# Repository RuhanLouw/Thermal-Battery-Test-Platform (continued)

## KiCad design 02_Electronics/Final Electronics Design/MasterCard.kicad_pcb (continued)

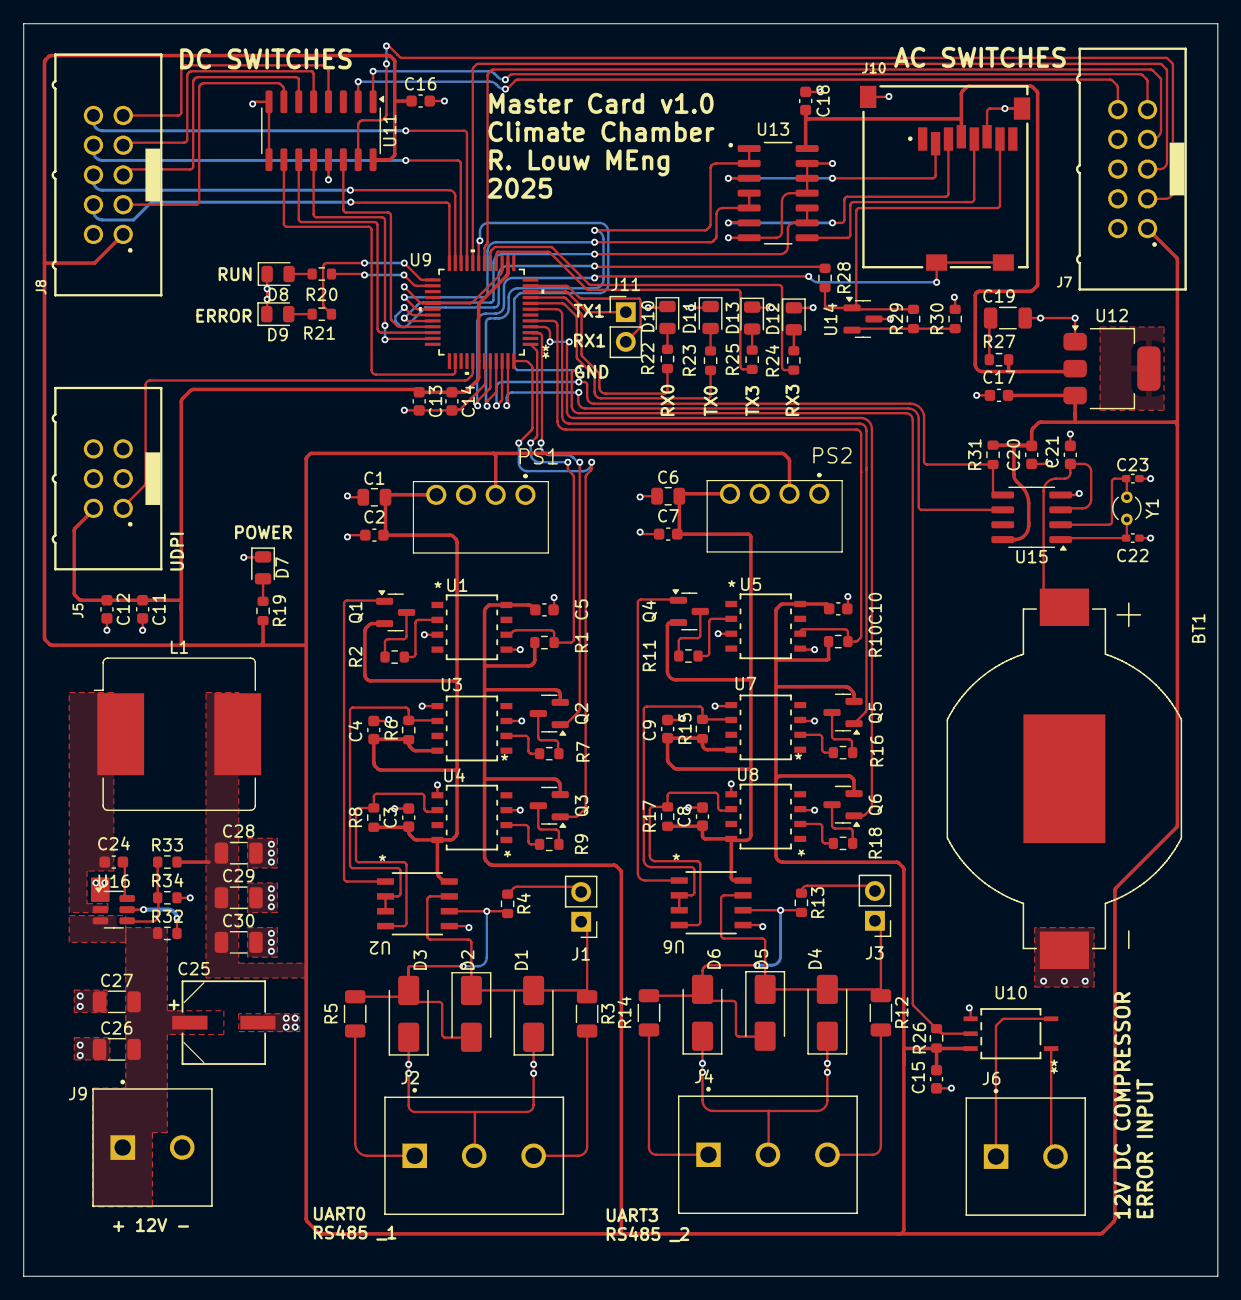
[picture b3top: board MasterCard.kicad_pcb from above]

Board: 2 copper layers, 102.0 x 107.0 mm, 115 parts (0 on the bottom side), 96 nets.

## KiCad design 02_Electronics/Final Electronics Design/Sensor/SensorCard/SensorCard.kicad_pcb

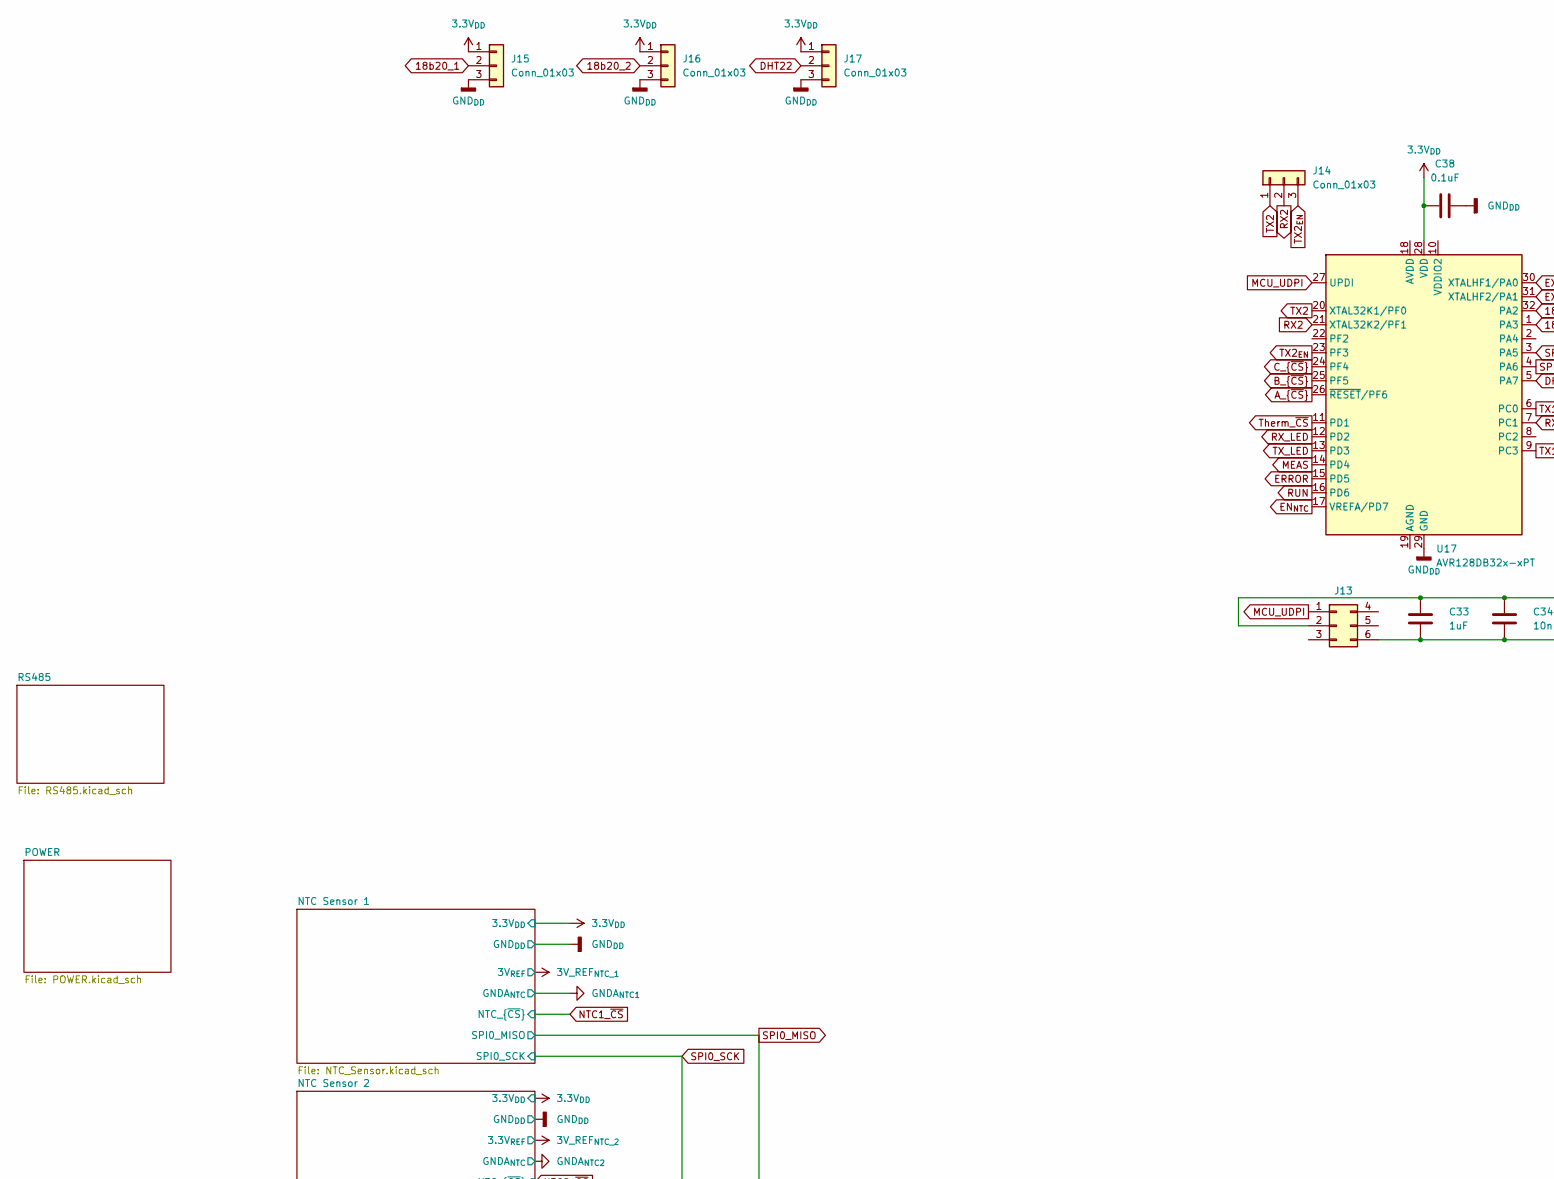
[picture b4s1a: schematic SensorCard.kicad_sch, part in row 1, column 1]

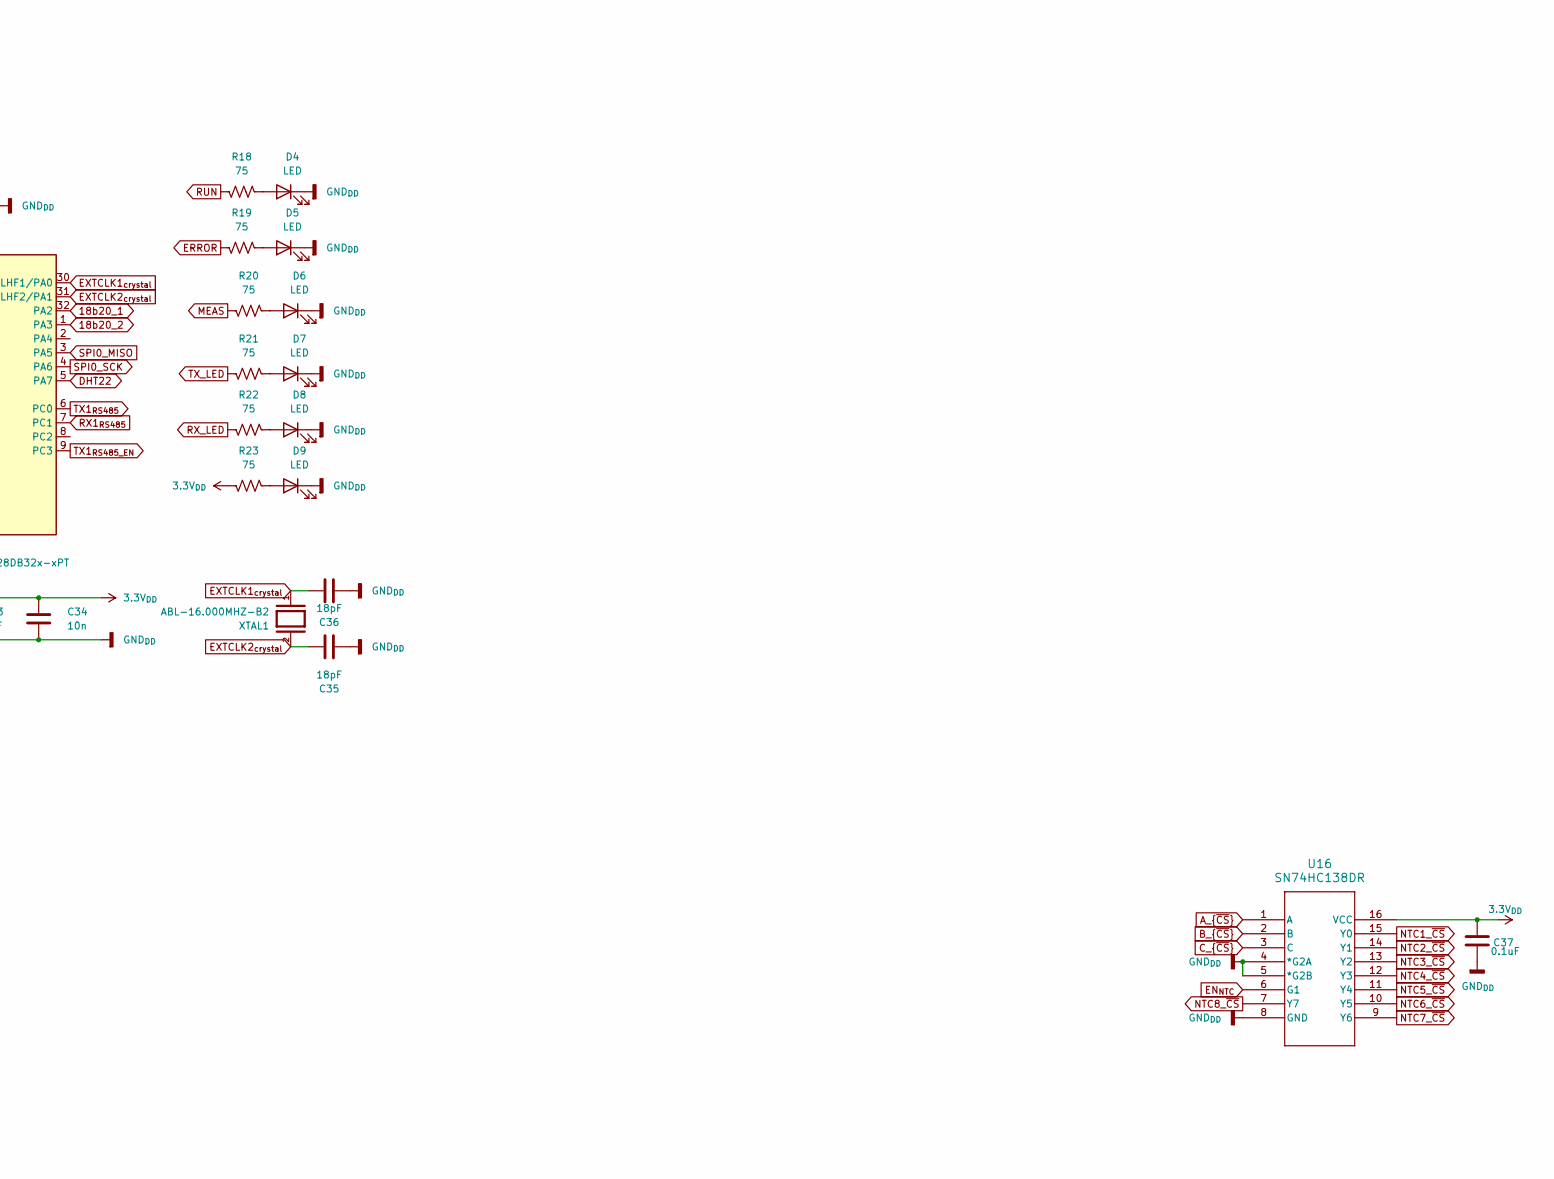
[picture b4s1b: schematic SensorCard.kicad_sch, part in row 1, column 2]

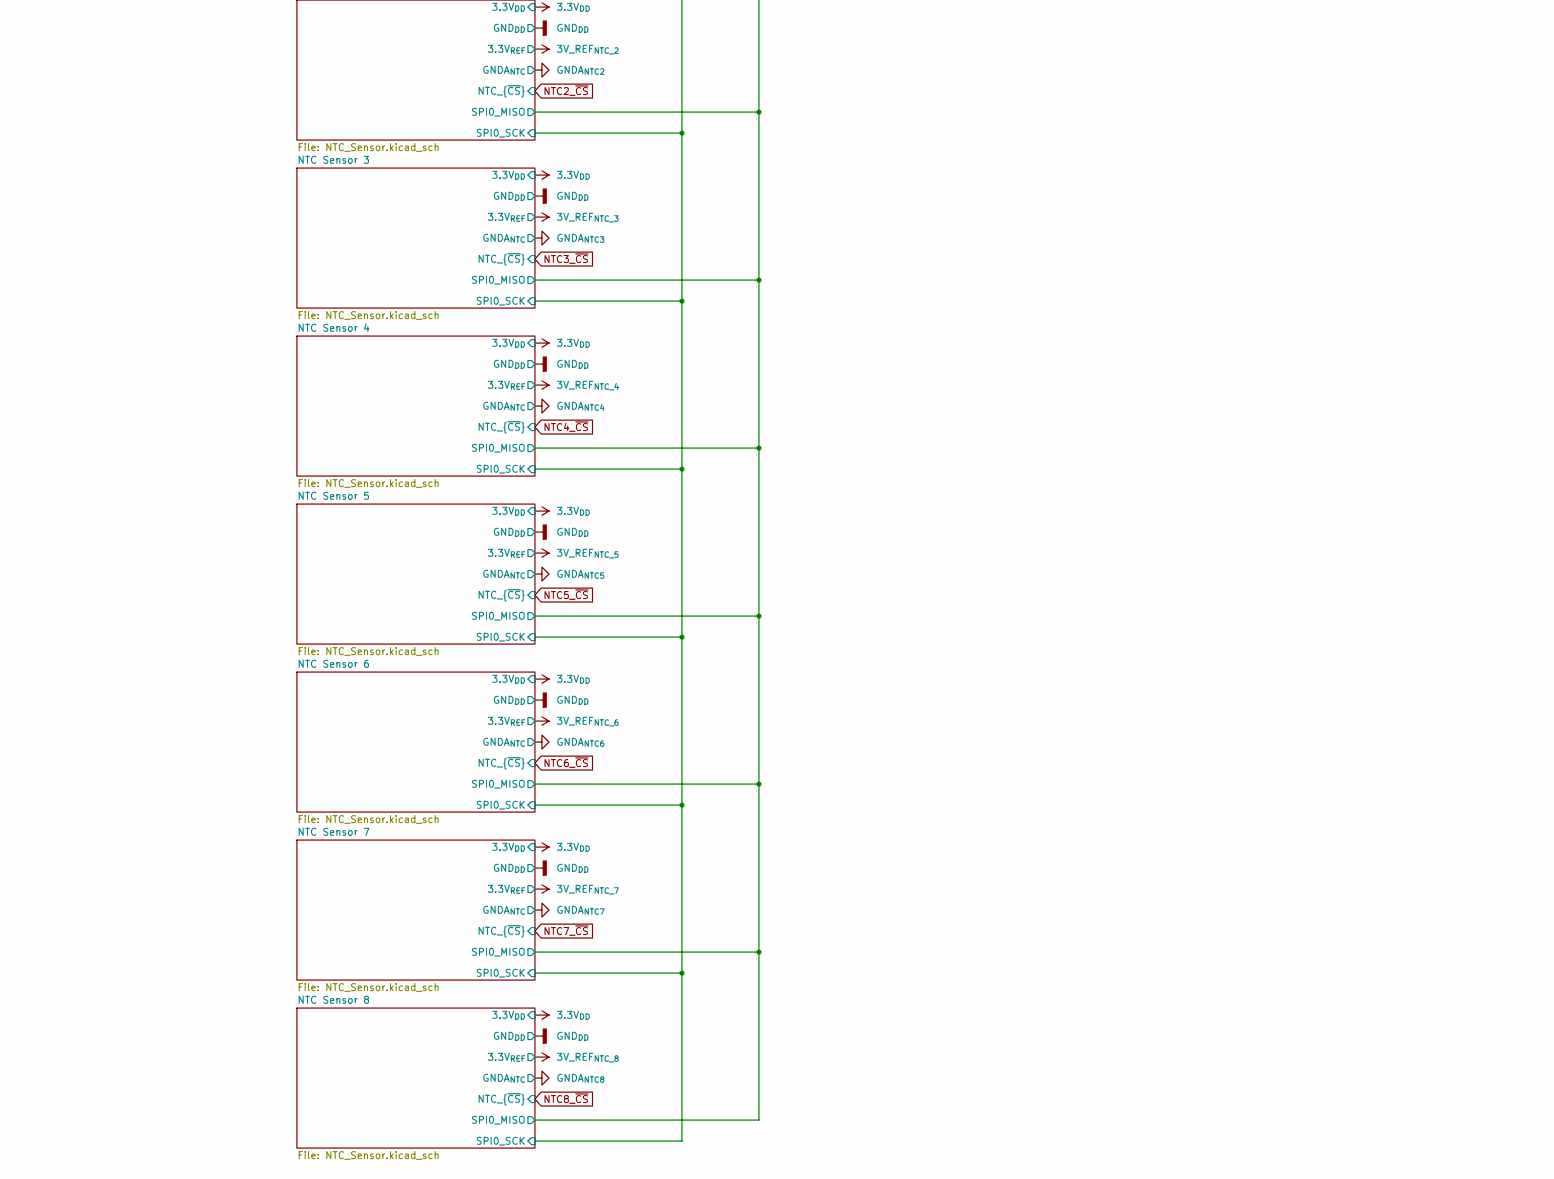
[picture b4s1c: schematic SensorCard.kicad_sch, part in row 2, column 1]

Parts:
C33: 1uF; C_0603_1608Metric
C34: 10n; C_0603_1608Metric
C35, C36: 18pF; C_0402_1005Metric
C37, C38: 0.1uF; C_0603_1608Metric
D4, D5, D6, D7, D8, D9: LED; LED_0805_2012Metric
J13: Conn_02x03_Top_Bottom; 61200621621
J14: Conn_01x03; PinHeader_1x03_P2.54mm_Vertical
J15, J16, J17: Conn_01x03; JST_XH_B3B-XH-A_1x03_P2.50mm_Vertical
R18, R19, R20, R21, R22, R23: 75; R_0603_1608Metric
U16: SN74HC138DR
U17: AVR128DB32x-xPT; TQFP-32_7x7mm_P0.8mm
XTAL1: ABL-16.000MHZ-B2; XTAL_HC49P488W46L1150T500H350; PARTREV 03.27.2018

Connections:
18b20_1: J15.2, U17.32 (PA2)
18b20_2: J16.2, U17.1 (PA3)
A_{~CS}: U16.1 (A), U17.26 (~RESET/PF6)
B_{~CS}: U16.2 (B), U17.25 (PF5)
C_{~CS}: U16.3 (C), U17.24 (PF4)
DHT22: J17.2, U17.5 (PA7)
EN_{NTC}: U16.6 (G1), U17.17 (VREFA/PD7)
ERROR: R19.1, U17.15 (PD5)
EXTCLK1_{crystal}: C36.1, U17.30 (XTALHF1/PA0), XTAL1.1
EXTCLK2_{crystal}: C35.1, U17.31 (XTALHF2/PA1), XTAL1.2
MCU_UDPI: J13.1, U17.27 (UPDI)
MEAS: R20.1, U17.14 (PD4)
NTC1_~CS: U16.15 (Y0); also elsewhere on the board
NTC2_~CS: U16.14 (Y1); also elsewhere on the board
NTC3_~CS: U16.13 (Y2); also elsewhere on the board
NTC4_~CS: U16.12 (Y3); also elsewhere on the board
NTC5_~CS: U16.11 (Y4); also elsewhere on the board
NTC6_~CS: U16.10 (Y5); also elsewhere on the board
NTC7_~CS: U16.9 (Y6); also elsewhere on the board
NTC8_~CS: U16.7 (Y7); also elsewhere on the board
unnamed: D4.2 (A), R18.2
unnamed: D5.2 (A), R19.2
unnamed: D6.2 (A), R20.2
unnamed: D7.2 (A), R21.2
unnamed: D8.2 (A), R22.2
unnamed: D9.2 (A), R23.2
RUN: R18.1, U17.16 (PD6)
RX1_{RS485}: U17.7 (PC1); also elsewhere on the board
RX2: J14.2, U17.21 (XTAL32K2/PF1)
RX_LED: R22.1, U17.12 (PD2)
SPI0_MISO: U17.3 (PA5); also elsewhere on the board
SPI0_SCK: U17.4 (PA6); also elsewhere on the board
TX1_{RS485_EN}: U17.9 (PC3); also elsewhere on the board
TX1_{RS485}: U17.6 (PC0); also elsewhere on the board
TX2: J14.1, U17.20 (XTAL32K1/PF0)
TX2_{EN}: J14.3, U17.23 (PF3)
TX_LED: R21.1, U17.13 (PD3)
Therm_~CS: U17.11 (PD1); also elsewhere on the board

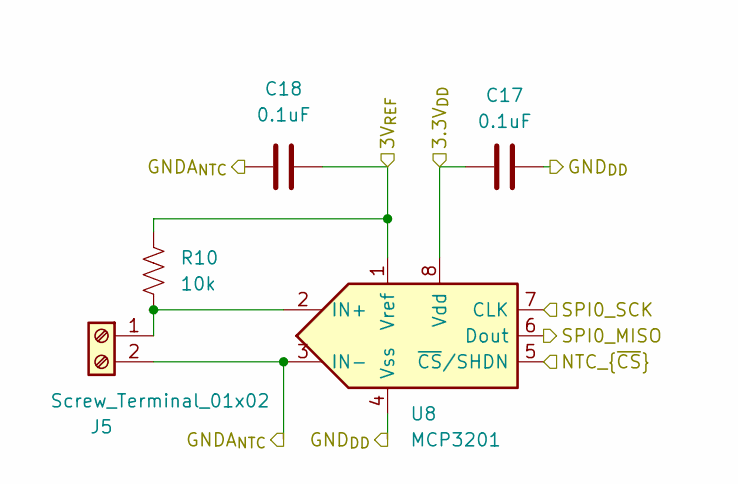
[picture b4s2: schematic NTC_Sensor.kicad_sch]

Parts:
C17, C18: 0.1uF; C_0603_1608Metric
J5: Screw_Terminal_01x02; TERM BLOCK 2P HORIZON 2.54MM PCB
R10: 10k; R_1206_3216Metric
U8: MCP3201; SOIC8-N_MC_MCH

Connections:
3V_REF_{NTC_1}: C18.2, R10.1, U8.1 (Vref); also elsewhere on the board
GNDA_{NTC1}: C18.1, J5.2, U8.3 (IN-); also elsewhere on the board
NTC1_~CS: U8.5 (~CS/SHDN); also elsewhere on the board
unnamed: J5.1, R10.2, U8.2 (IN+)
SPI0_MISO: U8.6 (Dout); also elsewhere on the board
SPI0_SCK: U8.7 (CLK); also elsewhere on the board

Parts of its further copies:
C19, C20, C21, C22, C23, C24, C25, C26, C27, C28, C29, C30, C31, C32: 0.1uF; C_0603_1608Metric
J6, J7, J8, J9, J10, J11, J12: Screw_Terminal_01x02; TERM BLOCK 2P HORIZON 2.54MM PCB
R11, R12, R13, R14, R15, R16, R17: 10k; R_1206_3216Metric
U9, U10, U11, U12, U13, U14, U15: MCP3201; SOIC8-N_MC_MCH

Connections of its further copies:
3V_REF_{NTC_2}: C20.2, R11.1, U9.1 (Vref); also elsewhere on the board
3V_REF_{NTC_3}: C22.2, R12.1, U10.1 (Vref); also elsewhere on the board
3V_REF_{NTC_4}: C24.2, R13.1, U11.1 (Vref); also elsewhere on the board
3V_REF_{NTC_5}: C26.2, R14.1, U12.1 (Vref); also elsewhere on the board
3V_REF_{NTC_6}: C28.2, R15.1, U13.1 (Vref); also elsewhere on the board
3V_REF_{NTC_7}: C30.2, R16.1, U14.1 (Vref); also elsewhere on the board
3V_REF_{NTC_8}: C32.2, R17.1, U15.1 (Vref); also elsewhere on the board
GNDA_{NTC2}: C20.1, J6.2, U9.3 (IN-); also elsewhere on the board
GNDA_{NTC3}: C22.1, J7.2, U10.3 (IN-); also elsewhere on the board
GNDA_{NTC4}: C24.1, J8.2, U11.3 (IN-); also elsewhere on the board
GNDA_{NTC5}: C26.1, J9.2, U12.3 (IN-); also elsewhere on the board
GNDA_{NTC6}: C28.1, J10.2, U13.3 (IN-); also elsewhere on the board
GNDA_{NTC7}: C30.1, J11.2, U14.3 (IN-); also elsewhere on the board
GNDA_{NTC8}: C32.1, J12.2, U15.3 (IN-); also elsewhere on the board
NTC2_~CS: U9.5 (~CS/SHDN); also elsewhere on the board
NTC3_~CS: U10.5 (~CS/SHDN); also elsewhere on the board
NTC4_~CS: U11.5 (~CS/SHDN); also elsewhere on the board
NTC5_~CS: U12.5 (~CS/SHDN); also elsewhere on the board
NTC6_~CS: U13.5 (~CS/SHDN); also elsewhere on the board
NTC7_~CS: U14.5 (~CS/SHDN); also elsewhere on the board
NTC8_~CS: U15.5 (~CS/SHDN); also elsewhere on the board
unnamed: J6.1, R11.2, U9.2 (IN+)
unnamed: J7.1, R12.2, U10.2 (IN+)
unnamed: J8.1, R13.2, U11.2 (IN+)
unnamed: J9.1, R14.2, U12.2 (IN+)
unnamed: J10.1, R15.2, U13.2 (IN+)
unnamed: J11.1, R16.2, U14.2 (IN+)
unnamed: J12.1, R17.2, U15.2 (IN+)
SPI0_MISO: U9.6 (Dout), U10.6 (Dout), U11.6 (Dout), U12.6 (Dout), U13.6 (Dout), U14.6 (Dout), U15.6 (Dout); also elsewhere on the board
SPI0_SCK: U9.7 (CLK), U10.7 (CLK), U11.7 (CLK), U12.7 (CLK), U13.7 (CLK), U14.7 (CLK), U15.7 (CLK); also elsewhere on the board

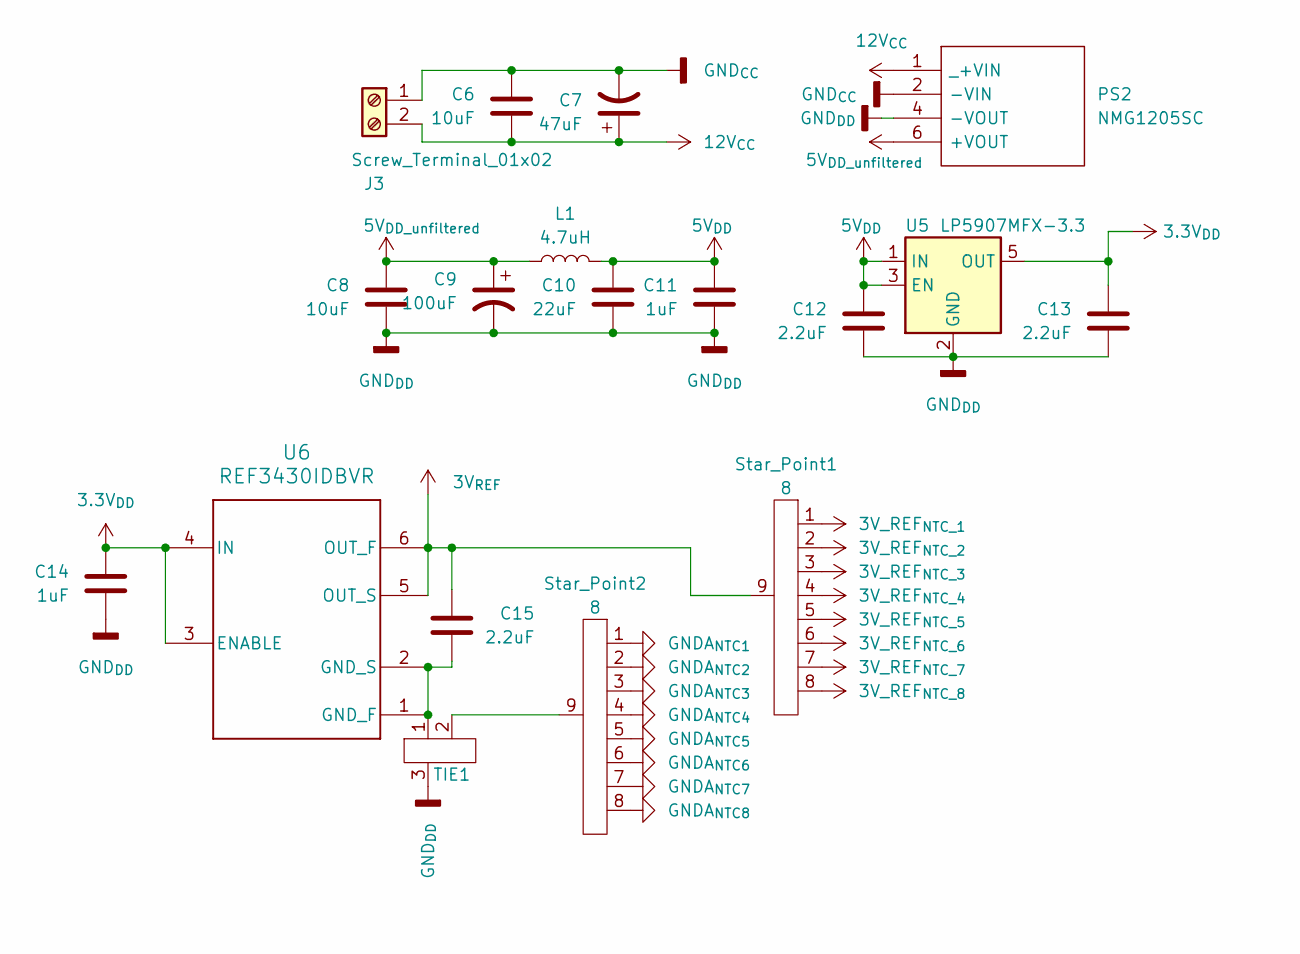
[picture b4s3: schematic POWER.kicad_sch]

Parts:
C6, C8: 10uF; C_0805_2012Metric
C7: 47uF; WCAP-ASLI_6.3X5.5_DXL_47uF
C9: 100uF; C_Radial_D6.3mm_H11.0mm_P2.50mm
C10: 22uF; C_1210_3225Metric
C11, C14: 1uF; C_0603_1608Metric
C12, C13, C15: 2.2uF; C_0603_1608Metric
J3: Screw_Terminal_01x02; TE_282857-2_screw
L1: 4.7uH; L_1210_3225Metric_Pad1.42x2.65mm_HandSolder_cad
PS2: NMG1205SC
Star_Point1, Star_Point2: 8; STARPOINT 9 ROUND PAD
TIE1: Star_Point_3
U5: LP5907MFX-3.3; SOT-23-5
U6: REF3430IDBVR; SOT-23-6

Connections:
3V_REF_{NTC_1}: Star_Point1.1 (tie_1); also elsewhere on the board
3V_REF_{NTC_2}: Star_Point1.2 (tie_2); also elsewhere on the board
3V_REF_{NTC_3}: Star_Point1.3 (tie_3); also elsewhere on the board
3V_REF_{NTC_4}: Star_Point1.4 (tie_3); also elsewhere on the board
3V_REF_{NTC_5}: Star_Point1.5; also elsewhere on the board
3V_REF_{NTC_6}: Star_Point1.6; also elsewhere on the board
3V_REF_{NTC_7}: Star_Point1.7; also elsewhere on the board
3V_REF_{NTC_8}: Star_Point1.8; also elsewhere on the board
3V_{REF}: C15.1, Star_Point1.9, U6.5 (OUT_S), U6.6 (OUT_F)
5V_{DD_unfiltered}: C8.1, C9.1, L1.2, PS2.6 (+VOUT); also elsewhere on the board
5V_{DD}: C10.1, C11.1, C12.1, L1.1, U5.1 (IN), U5.3 (EN)
12V_{CC}: C6.2, C7.1, J3.2, PS2.1 (_+VIN)
GNDA_{NTC1}: Star_Point2.1 (tie_1); also elsewhere on the board
GNDA_{NTC2}: Star_Point2.2 (tie_2); also elsewhere on the board
GNDA_{NTC3}: Star_Point2.3 (tie_3); also elsewhere on the board
GNDA_{NTC4}: Star_Point2.4 (tie_3); also elsewhere on the board
GNDA_{NTC5}: Star_Point2.5; also elsewhere on the board
GNDA_{NTC6}: Star_Point2.6; also elsewhere on the board
GNDA_{NTC7}: Star_Point2.7; also elsewhere on the board
GNDA_{NTC8}: Star_Point2.8; also elsewhere on the board
GND_{CC}: C6.1, C7.2, J3.1, PS2.2 (-VIN)
unnamed: C15.2, TIE1.1 (tie_1), U6.1 (GND_F), U6.2 (GND_S)
unnamed: Star_Point2.9, TIE1.2 (tie_2)

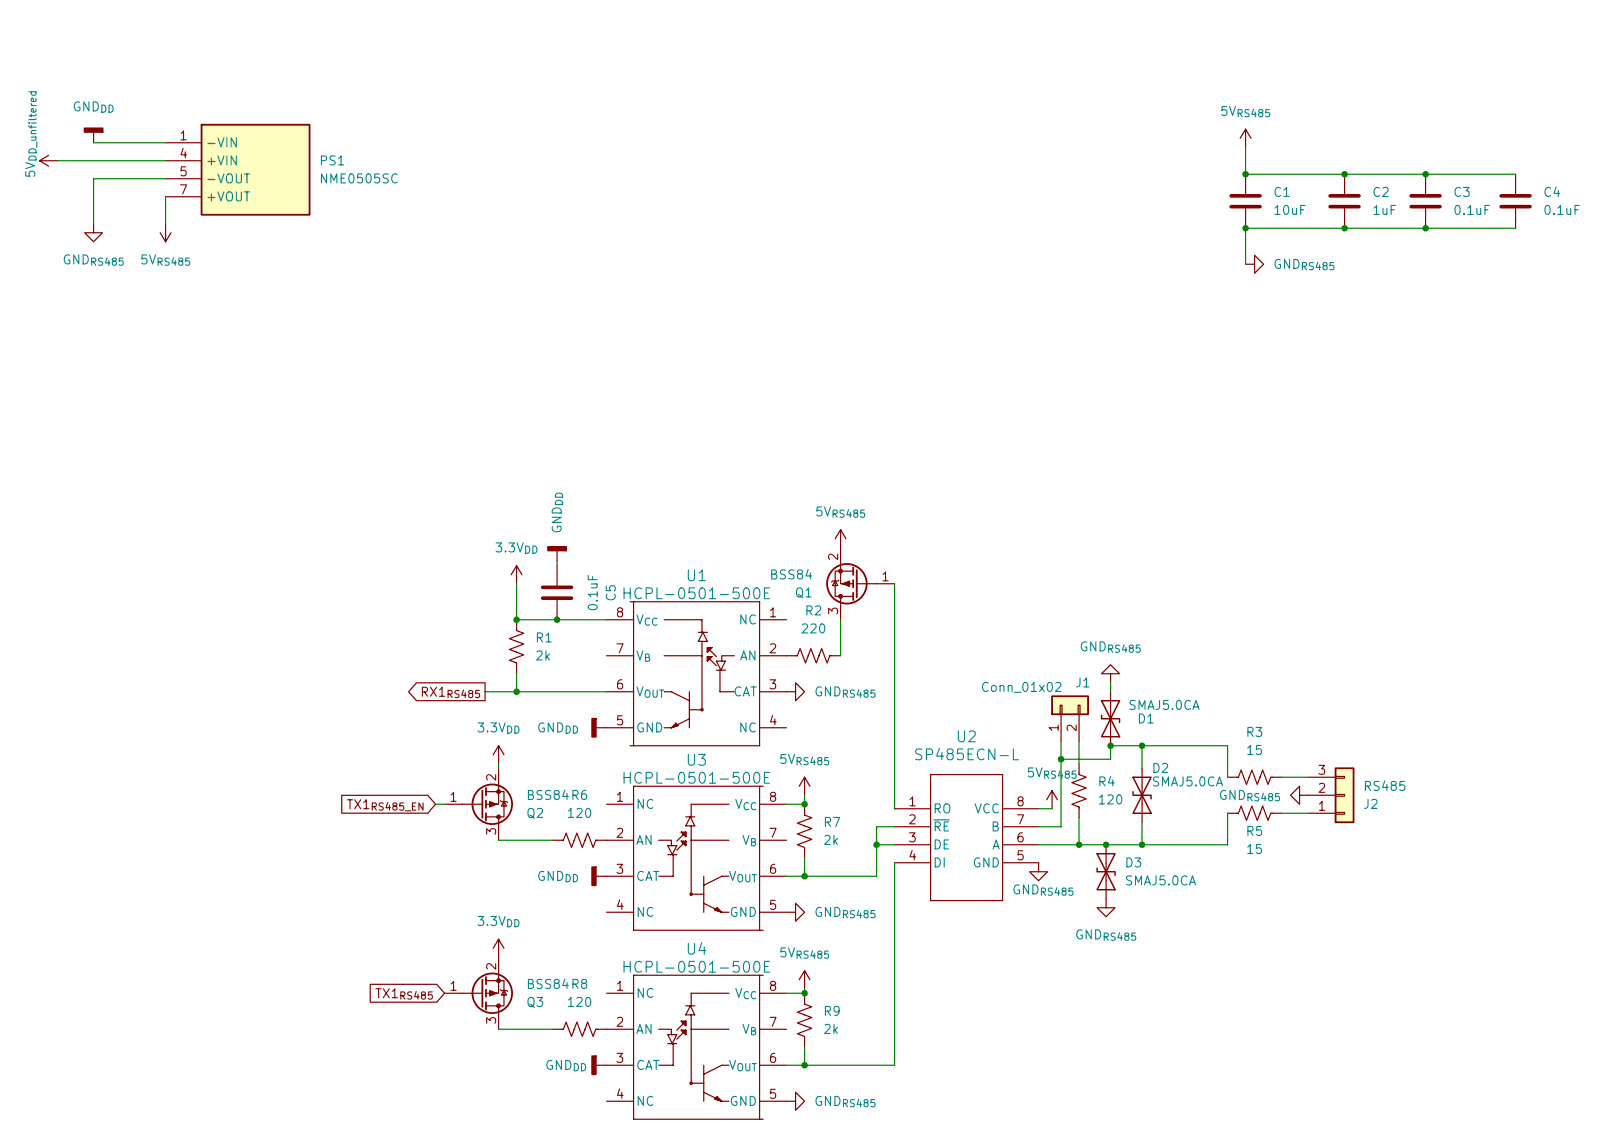
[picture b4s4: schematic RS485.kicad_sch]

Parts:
C1: 10uF; C_0805_2012Metric
C2: 1uF; C_0603_1608Metric
C3, C4, C5: 0.1uF; C_0603_1608Metric
D1, D2, D3: SMAJ5.0CA; D_SMA
J1: Conn_01x02; PinHeader_1x02_P2.54mm_Vertical
J2: RS485; TE_282857-3_screw
PS1: NME0505SC; Mouser Part Number 580-NME0505SC
Q1, Q2, Q3: BSS84; SOT-23
R1, R7, R9: 2k; R_0603_1608Metric
R2: 220; R_0603_1608Metric
R3, R5: 15; R_1206_3216Metric
R4, R6, R8: 120; R_0603_1608Metric
U1, U3, U4: HCPL-0501-500E; SO8_HCPL-0501-500_BRA
U2: SP485ECN-L; NSOIC-8

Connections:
5V_{DD_unfiltered}: PS1.4 (+VIN); also elsewhere on the board
5V_{RS485}: C1.1, C2.1, C3.1, C4.1, PS1.7 (+VOUT), Q1.2 (S), R7.2, R9.2, U2.8 (VCC), U3.8 (V_{CC}), U4.8 (V_{CC})
GND_{RS485}: C1.2, C2.2, C3.2, C4.2, D1.1 (A1), D3.1 (A1), J2.2, PS1.5 (-VOUT), U1.3 (CAT), U2.5 (GND), U3.5 (GND), U4.5 (GND)
unnamed: D1.2 (A2), D2.1 (A1), J1.1, R3.1, U2.7 (B)
unnamed: D2.2 (A2), D3.2 (A2), R4.2, R5.1, U2.6 (A)
unnamed: J1.2, R4.1
unnamed: J2.1, R5.2
unnamed: J2.3, R3.2
unnamed: Q1.3 (D), R2.1
unnamed: Q1.1 (G), U2.1 (RO)
unnamed: Q2.3 (D), R6.1
unnamed: Q3.3 (D), R8.1
unnamed: R2.2, U1.2 (AN)
unnamed: R7.1, U2.2 (~RE), U2.3 (DE), U3.6 (V_{OUT})
unnamed: R9.1, U2.4 (DI), U4.6 (V_{OUT})
unnamed: R6.2, U3.2 (AN)
unnamed: R8.2, U4.2 (AN)
RX1_{RS485}: R1.1, U1.6 (V_{OUT}); also elsewhere on the board
TX1_{RS485_EN}: Q2.1 (G); also elsewhere on the board
TX1_{RS485}: Q3.1 (G); also elsewhere on the board

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
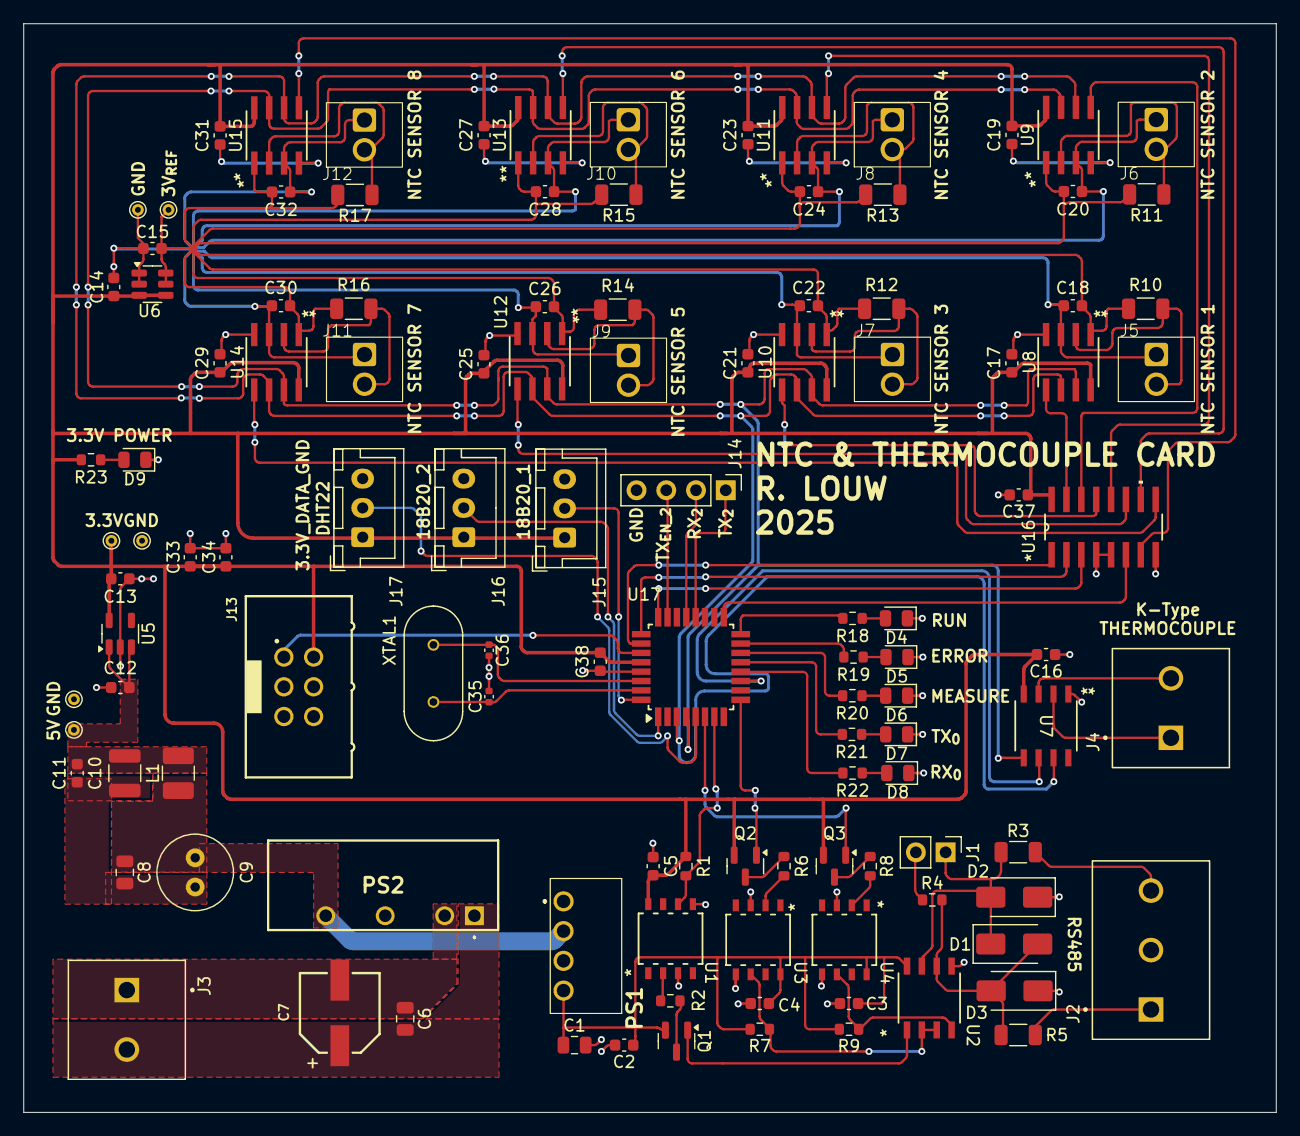
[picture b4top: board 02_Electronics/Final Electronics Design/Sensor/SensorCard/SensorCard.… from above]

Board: 2 copper layers, 107.0 x 93.0 mm, 113 parts (1 on the bottom side), 88 nets.

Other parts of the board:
C16: 0.1uF; C_0603_1608Metric
J4: Screw_Terminal_01x02; TE_282857-2_screw
U7: MAX31855KASA+T; 21-0041B_8_MXM

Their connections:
unnamed: J4.1, U7.2 (T-)
unnamed: J4.2, U7.3 (T+)
SPI0_MISO: U7.7 (SO); also elsewhere on the board
SPI0_SCK: U7.5 (SCK); also elsewhere on the board
Therm_~CS: U7.6 (*CS); also elsewhere on the board

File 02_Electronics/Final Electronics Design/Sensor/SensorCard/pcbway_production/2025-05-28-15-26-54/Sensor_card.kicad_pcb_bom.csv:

Designator,Quantity,Value,Footprint,Package,MPN,DNP,Mount_Type,Description,Sim.Pins,Height,Mouser Part Number,Mouser Price/Stock,Manufacturer_Name,PARTREV,STANDARD,MANUFACTURER
"C1, C6, C8",3,10uF,C_0805_2012Metric,,,,smt,10 µF ±10% 10V Ceramic Capacitor X7R 0805 (2012 Metric),,,,,,,,
C10,1,22uF,C_1210_3225Metric,,,,smt,CAP CER 22UF 16V X7R 1210,,,,,,,,
"C11, C14, C2, C33",4,1uF,C_0603_1608Metric,,,,smt,[C33]CAP CER 1UF 25V X7R 0603; [C2]CAP CER 1UF 10V X7R 0603,,,,,,,,
"C12, C13, C15",3,2.2uF,C_0603_1608Metric,,,,smt,CAP CER 2.2UF 25V X5R 0603,,,,,,,,
"C16, C17, C18, C19, C20, C21, C22, C23, C24, C25, C26, C27, C28, C29, C3, C30, C31, C32, C37, C38, C4, C5",22,0.1uF,C_0603_1608Metric,,,,smt,"[C37,C38]0.1 µF ±10% 50V Ceramic Capacitor X7R 0603 (1608 Metric); [C4,C5]Unpolarized capacitor",,,,,,,,
C34,1,10n,C_0603_1608Metric,,,,smt,Unpolarized capacitor,,,,,,,,
"C35, C36",2,18pF,C_0402_1005Metric,,,,smt,CAP CER 18PF 50V C0G/NP0 0402,,,,,,,,
C7,1,47uF,WCAP-ASLI_6.3X5.5_DXL_47uF,,,,smt,"47 µF 35 V Aluminum Electrolytic Capacitors Radial, Can - SMD 2000 Hrs @ 105°C",,,,,,,,
C9,1,100uF,C_Radial_D6.3mm_H11.0mm_P2.50mm,,,,tht,CAP ALUM 100UF 20% 35V RADIAL TH KEMET,,,,,,,,
"D1, D2, D3",3,SMAJ5.0CA,D_SMA,,,,smt,"400W bidirectional Transient Voltage Suppressor, 5.0Vr, SMA(DO-214AC)",,,,,,,,
"D4, D5, D6, D7, D8, D9",6,LED,LED_0805_2012Metric,,,,smt,LED GREEN CLEAR 0805 SMD,1=K 2=A,,,,,,,
J1,1,Conn_01x02,PinHeader_1x02_P2.54mm_Vertical,,,,tht,"Generic connector, single row, 01x02, script generated (kicad-library-utils/schlib/autogen/connector/)",,,,,,,,
"J10, J11, J12, J5, J6, J7, J8, J9",8,Screw_Terminal_01x02,TERM BLOCK 2P HORIZON 2.54MM PCB,,,,tht,"Generic screw terminal, single row, 01x02, script generated (kicad-library-utils/schlib/autogen/connector/)",,,,,,,,
J13,1,Conn_02x03_Top_Bottom,61200621621,,,,tht,"Generic connector, double row, 02x03, top/bottom pin numbering scheme (row 1: 1...pins_per_row, row2: pins_per_row+1 ... num_pins), script generated (kicad-library-utils/schlib/autogen/connector/)",,,,,,,,
J14,1,Conn_01x03,PinHeader_1x04_P2.54mm_Vertical,,,,tht,,,,,,,,,
"J15, J16, J17",3,Conn_01x03,JST_XH_B3B-XH-A_1x03_P2.50mm_Vertical,,,,tht,"Generic connector, single row, 01x03, script generated (kicad-library-utils/schlib/autogen/connector/)",,,,,,,,
J2,1,RS485,TE_282857-3_screw,,,,tht,"Generic connector, single row, 01x03, script generated (kicad-library-utils/schlib/autogen/connector/)",,,,,,,,
"J3, J4",2,Screw_Terminal_01x02,TE_282857-2_screw,,,,tht,"[J3]2 Position Wire to Board Terminal Block Horizontal with Board 0.200"" (5.08mm) Through Hole; [J4]Generic screw terminal, single row, 01x02, script generated (kicad-library-utils/schlib/autogen/connector/)",,,,,,,,
L1,1,4.7uH,L_1210_3225Metric_Pad1.42x2.65mm_HandSolder_cad,,,,smt,4.7 µH Unshielded Wirewound Inductor 800 mA 190mOhm Max 1210 (3225 Metric),,,,,,,,
PS1,1,NME0505SC,NME0505SC,,NME0505SC,,tht,"Murata Power Solutions NME 1W Isolated DC-DC Converter Through Hole, Vin 4.5  5.5 V dc, Vout 5V dc",,10.25,580-NME0505SC,https://www.mouser.co.uk/ProductDetail/Murata-Power-Solution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,Murata Electronics,,,
PS2,1,NMG1205SC,NMG1205SC,,,,tht,Isolated DC/DC Converters - Through Hole 2W TH 2W 12-5V SIP DC/DC,,,,,,,,
"Q1, Q2, Q3",3,BSS84,SOT-23,,,,smt,"-0.13A Id, -50V Vds, P-Channel MOSFET, SOT-23",,,,,,,,
"R1, R7, R9",3,2k,R_0603_1608Metric,,,,smt,"Resistor, US symbol",,,,,,,,
"R10, R11, R12, R13, R14, R15, R16, R17",8,10k,R_1206_3216Metric,,,,smt,"10 kOhms ±0.01% 0.25W, 1/4W Chip Resistor 1206 (3216 Metric) Automotive AEC-Q200 Thin Film",,,,,,,,
"R18, R19, R20, R21, R22, R23",6,75,R_0603_1608Metric,,,,smt,RES SMD 75 OHM 1% 1/10W 0603,,,,,,,,
R2,1,220,R_0603_1608Metric,,,,smt,"Resistor, US symbol",,,,,,,,
"R3, R5",2,15,R_1206_3216Metric,,,,smt,"Resistor, US symbol",,,,,,,,
"R4, R6, R8",3,120,R_0603_1608Metric,,,,smt,"Resistor, US symbol",,,,,,,,
"Star_Point1, Star_Point2",2,8,STARPOINT 9 ROUND PAD,,,,smt,,,,,,,,,
"U1, U3, U4",3,HCPL-0501-500E,SO8_HCPL-0501-500_BRA,,,,smt,,,,,,,,,
"U10, U11, U12, U13, U14, U15, U8, U9",8,MCP3201,SOIC8-N_MC_MCH,,,,smt,"2.7V 12-Bit A/D Converter with SPI™ Serial Interface, PDIP-8/SOIC-8/MSOP-8/TSSOP-8",,,,,,,,
U16,1,SN74HC138DR,SN74HC138DR,,,,smt,Decoder/Demultiplexer 1 x 3:8 16-SOIC,,,,,,,,
U17,1,AVR128DB32x-xPT,TQFP-32_7x7mm_P0.8mm,,,,smt,"24MHz, 128kB Flash, 16kB SRAM, EEPROM with Op Amps and Multi-Voltage I/O, TQFP-32",,,,,,,,
U2,1,SP485ECN-L,NSOIC-8,,,,smt,RS485,,,,,,,,
U5,1,LP5907MFX-3.3,SOT-23-5,,,,smt,"250-mA Ultra-Low-Noise Low-IQ LDO, 3.3V, SOT-23",,,,,,,,
U6,1,REF3430IDBVR,SOT-23-6,,,,smt,Series Voltage Reference IC Fixed 3V V ±0.05% 10 mA SOT-23-6,,,,,,,,
U7,1,MAX31855KASA+T,21-0041B_8_MXM,,,,smt,,,,,,,,,
XTAL1,1,ABL-16.000MHZ-B2,XTAL_HC49P488W46L1150T500H350,,,,tht,16 MHz ±20ppm Crystal 18pF 40 Ohms HC-49/US,,,,,,03.27.2018,IPC-7351B,Abracon
